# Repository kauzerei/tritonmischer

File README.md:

# Tritonmischer

Matrix audio mixer with 3 stereo inputs and 3 stereo outputs.

You can find the [documentation here on GitHub pages](https://kauzerei.github.io/tritonmischer/).

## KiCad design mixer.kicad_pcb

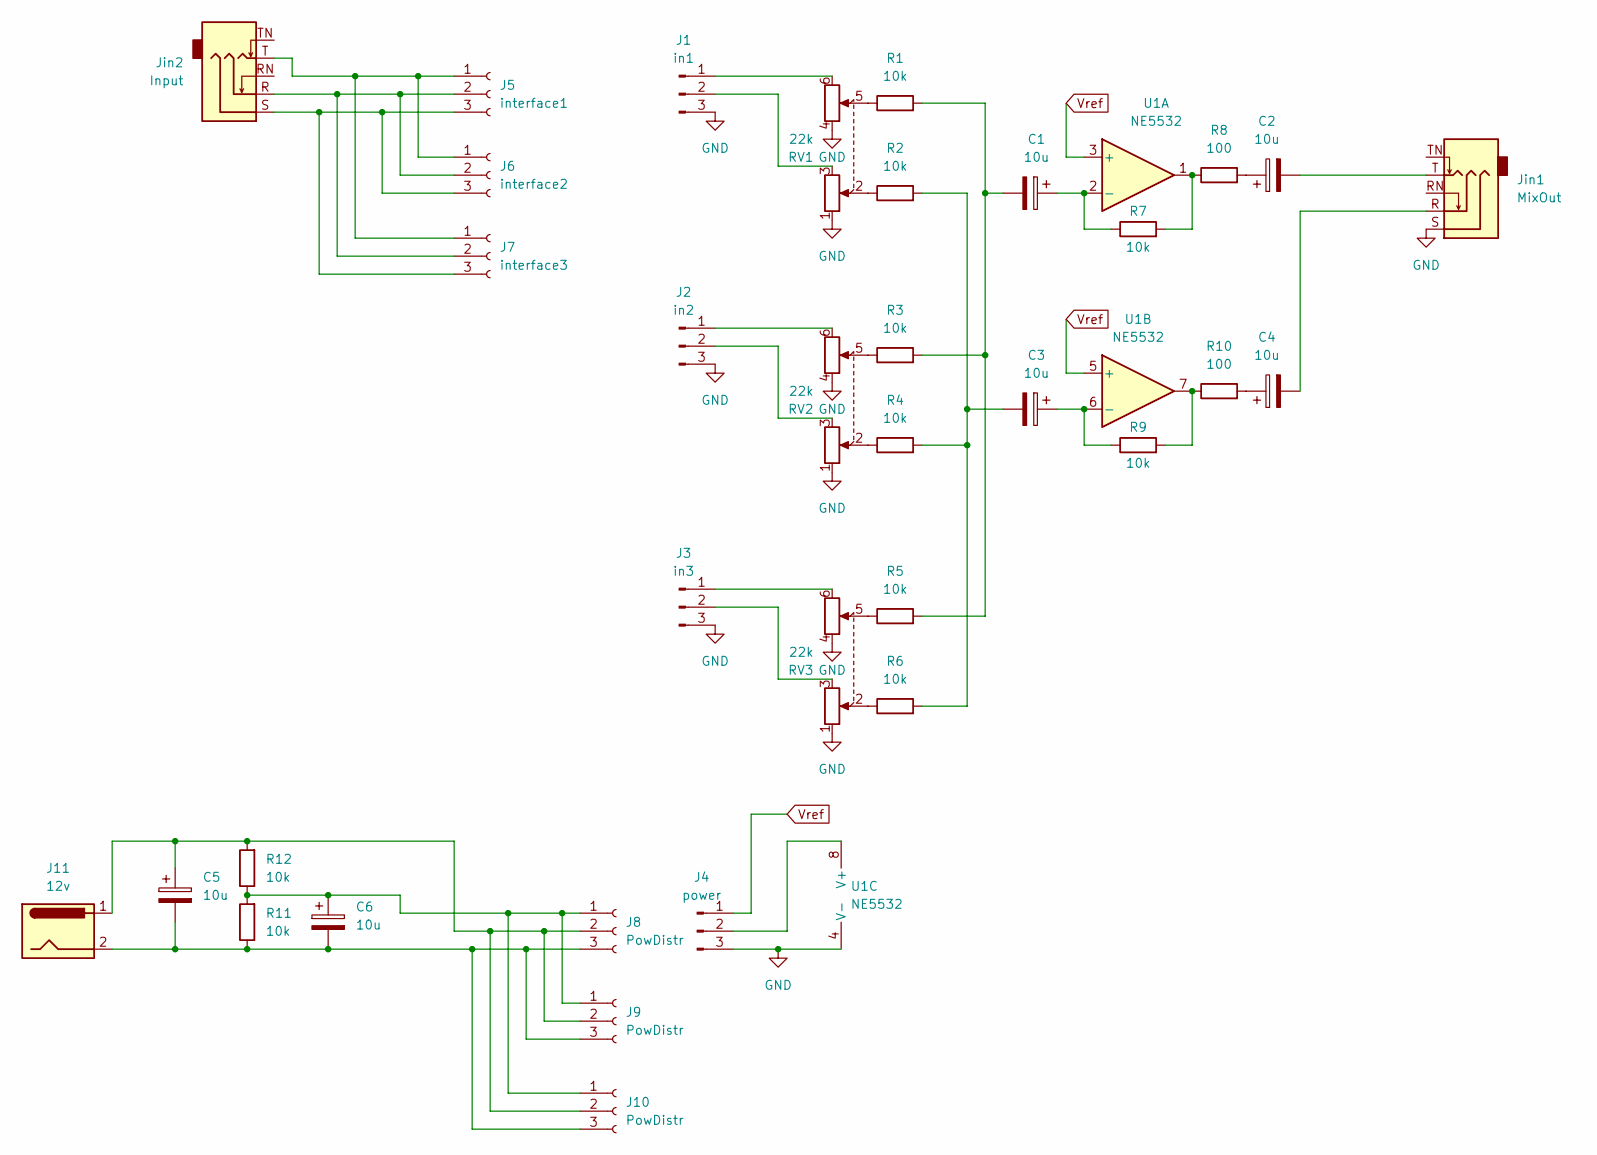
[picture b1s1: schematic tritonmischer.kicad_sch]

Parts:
C1, C2, C3, C4, C5, C6: 10u; CP_Radial_D8.0mm_P5.00mm
J1: in1; PinHeader_1x03_P2.54mm_Vertical
J2: in2; PinHeader_1x03_P2.54mm_Vertical
J3: in3; PinHeader_1x03_P2.54mm_Vertical
J4: power; PinHeader_1x03_P2.54mm_Vertical
J5: interface1; PinSocket_1x03_P2.54mm_Vertical
J6: interface2; PinSocket_1x03_P2.54mm_Vertical
J7: interface3; PinSocket_1x03_P2.54mm_Vertical
J8, J9, J10: PowDistr; PinSocket_1x03_P2.54mm_Vertical
J11: 12v; JWT_A3963_1x02_P3.96mm_Vertical
Jin1: MixOut; Jack_3.5mm_CUI_SJ1-3525N_Horizontal
Jin2: Input; Jack_3.5mm_CUI_SJ1-3525N_Horizontal
R1, R2, R3, R4, R5, R6: 10k; R_Axial_DIN0204_L3.6mm_D1.6mm_P5.08mm_Vertical
R7, R9, R12: 10k; R_Axial_DIN0204_L3.6mm_D1.6mm_P2.54mm_Vertical
R8, R10: 100; R_Axial_DIN0204_L3.6mm_D1.6mm_P2.54mm_Vertical
R11: 10k; R_Axial_DIN0204_L3.6mm_D1.6mm_P5.08mm_Horizontal
RV1, RV2, RV3: 22k; Potentiometer_Alps_RK163_Dual_Horizontal
U1: NE5532; DIP-8_W7.62mm

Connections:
GND: J1.3, J2.3, J3.3, J4.3, Jin1.S, RV1.1, RV1.4, RV2.1, RV2.4, RV3.1, RV3.4, U1.4 (V-)
unnamed: C1.2, R1.2, R3.2, R5.2
unnamed: C2.1, R8.2
unnamed: C2.2, Jin1.T
unnamed: C3.2, R2.2, R4.2, R6.2
unnamed: C4.1, R10.2
unnamed: C4.2, Jin1.R
unnamed: J1.1, RV1.6
unnamed: J1.2, RV1.3
unnamed: J2.1, RV2.6
unnamed: J2.2, RV2.3
unnamed: J3.1, RV3.6
unnamed: J3.2, RV3.3
unnamed: J4.2, U1.8 (V+)
unnamed: J5.1, J6.1, J7.1, Jin2.T
unnamed: J5.2, J6.2, J7.2, Jin2.R
unnamed: J5.3, J6.3, J7.3, Jin2.S
unnamed: C6.1, J8.1, J9.1, J10.1, R11.2, R12.1
unnamed: C5.1, J8.2, J9.2, J10.2, J11.1, R12.2
unnamed: C5.2, C6.2, J8.3, J9.3, J10.3, J11.2, R11.1
unnamed: R1.1, RV1.5
unnamed: R2.1, RV1.2
unnamed: R3.1, RV2.5
unnamed: R4.1, RV2.2
unnamed: R5.1, RV3.5
unnamed: R6.1, RV3.2
unnamed: R7.2, R8.1, U1.1
unnamed: R9.2, R10.1, U1.7
unnamed: C1.1, R7.1, U1.2 (-)
unnamed: C3.1, R9.1, U1.6 (-)
Vref: J4.1, U1.3 (+), U1.5 (+)

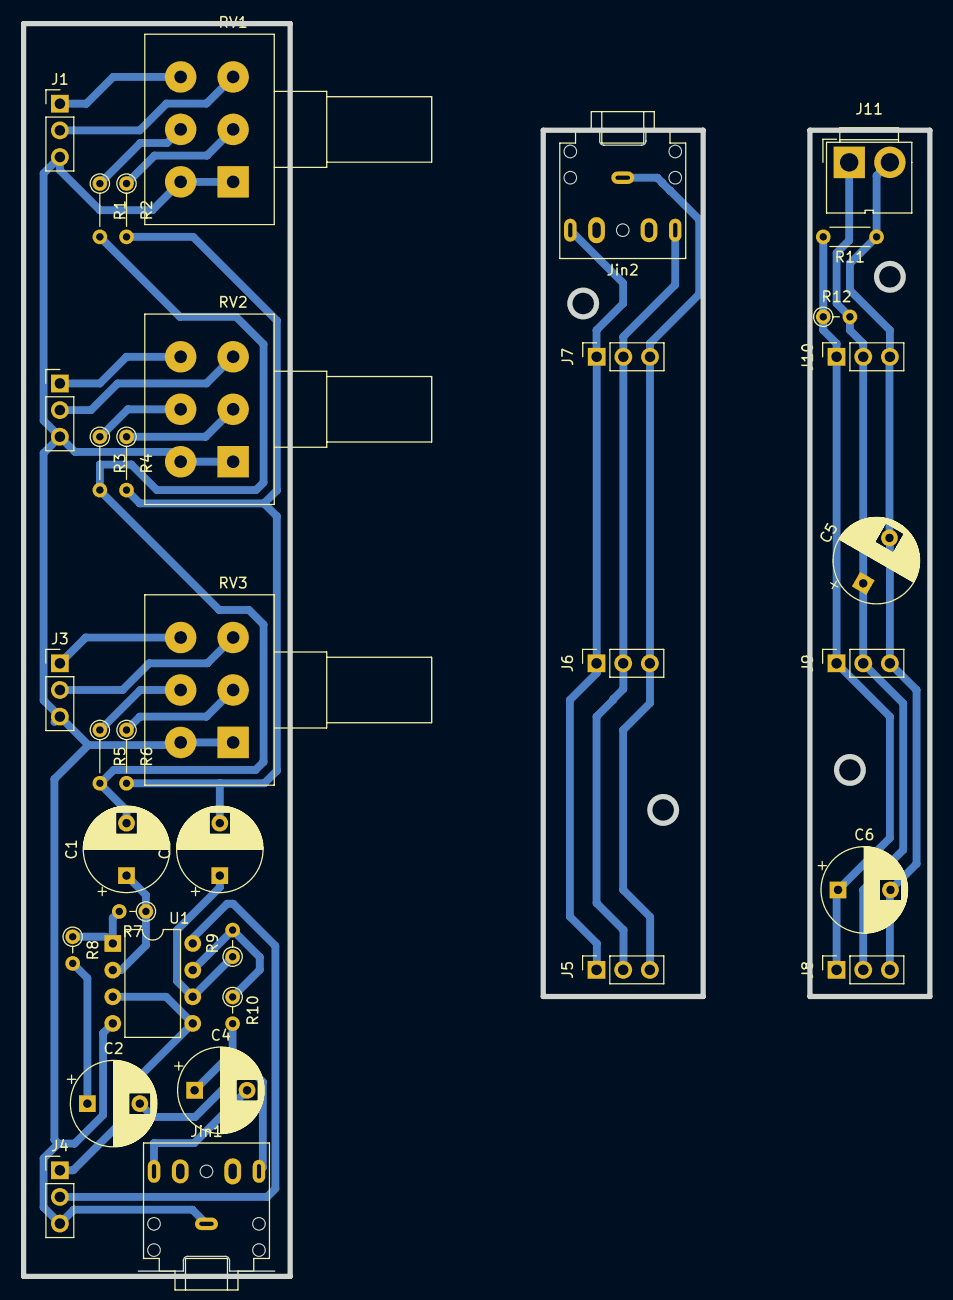
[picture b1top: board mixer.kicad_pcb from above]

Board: 2 copper layers, 86.4 x 119.4 mm, 35 parts (0 on the bottom side), 31 nets.

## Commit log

2024-01-27 publish tested schematics
2024-01-27 start creating box
2024-01-31 add box
2024-01-31 update box
2024-02-03 rename files based on pun
2024-02-05 add usual docs and workflow stuff
2024-02-05 wrong default branch name
2024-02-05 add scad workflow
